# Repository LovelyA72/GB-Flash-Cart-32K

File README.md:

This is an easy to make gameboy 32KB cartridge.

It is a heavily modified version of roybaer/gb_cartridge with SRAM and battery being removed.

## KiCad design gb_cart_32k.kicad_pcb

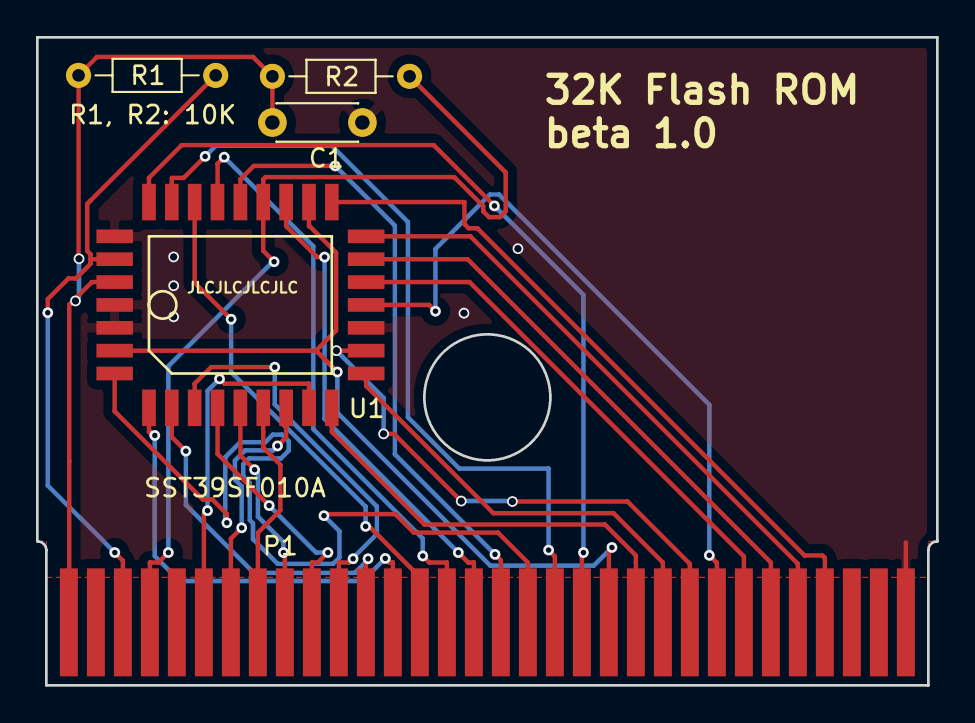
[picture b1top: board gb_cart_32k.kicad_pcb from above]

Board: 2 copper layers, 50.0 x 36.0 mm, 5 parts (0 on the bottom side), 28 nets.

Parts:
C1: 100n; C_Disc_D4.3mm_W1.9mm_P5.00mm
P1: GB_CART_CONN; GB_CART_EDGE
R1, R2: 10K; R_Axial_DIN0204_L3.6mm_D1.6mm_P7.62mm_Horizontal
U1: SST39SF010; PLCC-32

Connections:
A0: P1.6, U1.12
A1: P1.7, U1.11
A2: P1.8, U1.10
A3: P1.9, U1.9
A4: P1.10, U1.8
A5: P1.11, U1.7
A6: P1.12, U1.6
A7: P1.13, U1.5
A8: P1.14, U1.27
A9: P1.15, U1.26
A10: P1.16, U1.23
A11: P1.17, U1.25
A12: P1.18, U1.4
A13: P1.19, U1.28
A14: P1.20, U1.29
A15: P1.21, U1.3, U1.22
D0: P1.22, U1.13
D1: P1.23, U1.14
D2: P1.24, U1.15
D3: P1.25, U1.17
D4: P1.26, U1.18
D5: P1.27, U1.19
D6: P1.28, U1.20
D7: P1.29, U1.21
GND: C1.2, P1.32, U1.1, U1.2, U1.16, U1.30
ROM_OE: P1.4, R2.2, U1.24
VCC: C1.1, P1.1, R1.1, R2.1, U1.32
WE: P1.3, R1.2, U1.31

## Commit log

2020-05-21 add README.md

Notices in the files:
gb_cart_32k.kicad_pcb:
CC BY-NC-SA 4.0
